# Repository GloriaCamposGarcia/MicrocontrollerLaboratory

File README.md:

# Microcontroller Laboratory :)

## Introduction

Microcontrollers are all around  he world. Each day, Microcontrollers, are more present in the many aspects of our lives: in our work, inside our houses, and in more. We can find them controlling small devices like cellphones, microwaves, washing machines, and televisions.

A microcontroller is one device or chip that is used to govern one or more processes. For example, the controller that regulates the room temperature of an air conditioner; it has a sensor that continuously measures the internal temperature and, when the preset limits are exceeded, it generates the necessary signals to adjust the temperature.

## State of the Art

### The practices and the PIC microcontroller

The main objective of this practices is to provide students the foundation to fully understand the operation of the PIC18F45K50 microcontroller. This will be achieved through 11 documents that will guide the reader to create their own electronic card or Printed Circuit Board (PCB) and to be able to program it; in order to, execute different functions.

The advantages of ta PIC microcontroller to others on the market, which is why it will be used throughout this manual, are as follows:

- Easy to operate.
- There is enough documentation to work with it and it’s easy to obtain it.
- The price is comparatively lower than its competitors.
- It has a high operating speed.
- Development tools are cheap and easy to use.
- There are a variety of hardware that can record, erase and check the behavior of PIC.
- Once you learn to handle a PIC, it will easier to handle any other models of microcontrollers.

### KiCad EDA Software

KiCad is an open source software suite for Electronic Design Automation (EDA). The programs handle Schematic Capture,
and PCB Layout with Gerber output. The suite runs on Windows, Linux and macOS and is licensed under GNU GPL v3. The
first release date was in 1992 by its original author, Jean-Pierre Charras, but is now currently under development by
the KiCad Developers Team.

## Evaluation

- Demonstation  ... 60%
- Report .......... 40%

## Submission

Every submission must be in your own github repository. If you which you could fork this as skeleton. All pull request
will be denied.

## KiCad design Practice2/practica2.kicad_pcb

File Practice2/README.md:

# Practice 2. Developiong the PCB (Layout)

## Objectives

Develop the connection diagrams (layout) from the schematic diagram.

## Introduction

Microcontrollers are all around  he world. Each day, Microcontrollers, are more present in the many aspects of our lives: in our work, inside our houses, and in more. We can find them controlling small devices like cellphones, microwaves, washing machines, and televisions.

A microcontroller is one device or chip that is used to govern one or more processes. For example, the controller that regulates the room temperature of an air conditioner; it has a sensor that continuously measures the internal temperature and, when the preset limits are exceeded, it generates the necessary signals to adjust the temperature.

## State of the Art

### The practices and the PIC microcontroller

The main objective of this practices is to provide students the foundation to fully understand the operation of the PIC18F45K50 microcontroller. This will be achieved through 11 documents that will guide the reader to create their own electronic card or Printed Circuit Board (PCB) and to be able to program it; in order to, execute different functions.

The advantages of ta PIC microcontroller to others on the market, which is why it will be used throughout this manual, are as follows:

- Easy to operate.
- There is enough documentation to work with it and it’s easy to obtain it.
- The price is comparatively lower than its competitors.
- It has a high operating speed.
- Development tools are cheap and easy to use.
- There are a variety of hardware that can record, erase and check the behavior of PIC.
- Once you learn to handle a PIC, it will easier to handle any other models of microcontrollers.

### KiCad EDA Software

KiCad is an open source software suite for Electronic Design Automation (EDA). The programs handle Schematic Capture,
and PCB Layout with Gerber output. The suite runs on Windows, Linux and macOS and is licensed under GNU GPL v3. The
first release date was in 1992 by its original author, Jean-Pierre Charras, but is now currently under development by
the KiCad Developers Team. 

## Results

In this section, you must report the outcomes of the laboratory activities.

### Follow the next 'Project Configuration' Steps

1. In  the  same  project  from  practice  1,  click  on  the  icon ‘Assign PCB footprints to schematic symbols’.  By  doing  so,  you  will  be  able  to  watch  the  footprints associations in a list format. ***NOTE:*** *If a ***‘Confirmation’*** window pops to reassign all the components to a new library format, click ‘No.’*

2. Now it is time to add the corresponding libraries to the Cvpcbprogram.   Download from [here](./modules)  the modules   needed   for   the   project.   Click   on Preferences→Manage Footprint Libraries...and  in this  way  you  will  be  able  to  add  the  modules  from the folder  named  ‘modules.’  Click  on  ‘Project  Specific Libraries...’  tab,  then  click  on  the  button  ‘Browse Libraries...’ and search for the folder  where  you  save the modules. Select all the files and click ‘OK.’Fig.  1 shows the result of the added modules. NOTE:Your KiCad EDA Software must be in english to add the modules.

3. Once  that  is  done,  you  must  associate  the  list  of components  with  its  respective  footprint using Table  I for  guidance.  Be  sure  to  activate  the  option  ‘Filter footprints  list  by  library’ from  the Cvpcbtoolbar. To associate  the  components  showed  in  the middle  column,  double  click  with  their  corresponding footprint from the right column. ***NOTE:*** *Search  all  the  footprints  in  the*  ***‘user’*** *and * 
***‘discrete’*** * added libraries that should be found at the end of the list.*

4. Save   your modifications  by  clicking  **‘Apply,  Save Schematic & Continue,’ and then click ‘OK.’**
5. After that, you may close the Cvpcband go back to the EESchema (Schematic  Editor.)  Save  your  project  by clicking   on File→Save.   Close   the   editor   of   the Schematic and switch back to the **‘Project Manager.’**

6. Once you have the design of the circuit on the schematic, it is time to generate the **‘layout’** of our PCB  using the Netlist  file. On  the Project  Manager program  from KiCad, click on the icon **‘PCB layout editor’** . A new window will appear from the PCBNew. Click **‘Yes’** in the confirmation window.
7. On  the  toolbar  menu  from  the PCBNew click  on  the **‘Page  Settings  for  paper  size  and  texts’**
and modify the size settings to **‘USLetter 8.5x11in.’**

8. After  that,  it  will be  time  to  focus  more  on  design concepts.  You  may  do  so  by  opening  the
menu  of **‘Setup→Design Rules...’**. On   it,   some   final   design characteristics will appear with many millimeter values. Between   them,   you   should   find  the  **‘Clearance’** specification  which  is  the  smallest  spaces  that  it  must exist  between  the tracks  on the  PCB.  You  shall  set the value of this cell to 0.508 mm (0.020 inches.) Next, we set  a  value  of 1.200  mm  (0.047244 inches)on the  cell of **‘Track Width.’** 

9. Switch now to the ‘Global Design Rules’ tab and write, if needed, the minimum values for each an every one of the parameters on the ‘Minimum Allowed Values’ box. Click ‘OK.’

10. Time  to  import  the  Netlist  file.  Go  to  the  toolbar ‘Tools→Update  PCB  from  Schematic...’  and  then click on ‘Update  PCB.’ When  you  close  the  window all the components will appear on the screen.

11.Check in the ‘Layers Manager’ window (located at the right  part  of  your  screen) that all  the needed  boxes  are
checked, as shown:

11.Check in the ‘Layers Manager’ window (located at the right  part  of  your  screen) that all  the needed  boxes  are checke

12. Now you  have  to  define  the  limits  of  the  PCB.  First, highlight  the  ‘Edge.Cuts’  layer.  Then,  select  the  ‘Add  graphic lines’ tool and began to trace the original measures of your copper board (15x20 cm.) You must also define the  cutting  area;  do  not  forget  to  add  a  2.5  cm  margin around the board. To measure the lines, you can use the ‘Add dimension’ tool located on the right.

13. It is your turn to move all the components in the circuit in  order  to  avoid  any  track  intersection  inside  the working   area.   You   can   move   the   components   by positioning your mouse pointer above it and pressing the key [G]. All the components are connected to each other by a group of wires called ratsnest. Make sure that the icon  of  **‘Hide  board  ratsnest’** located  in  the toolbar of the left is highlighted.

14. Now you must link all the connections of you PCB. But before  that,  you  must  change  the  drawing  option  from the right toolbar from ‘Edge.Cuts’ to ‘B.Cu (PgDn)’ (B->Bottom, Cu->Copper.).

15. Start to connect your tracks to each and every one pin on the schematic by using the icon ‘Route Tracks’. Trace  all  the  routes  for  each  net  or  connection  in  your PCB design.

16. Once  your  are  done,  save  your  layout  File->Save  or using the command [Ctrl + S].

17. Your board must look like:

### Report
For this practice, modify only the Conclusion section. Commit an push the changes on the fork of this repository and add
upload the link on Canvas.

### File uploads
Commit and push the files with extensions .pro and .kicad_pcb created once you completed all the steps of the document in the repository.

### Demonstration
Screenshot the image of the complete schematic and upload it at the repository.

## Conclusion

La parte de los footprimts fue la parte mas complicada debido a que no me identificaba las librerias y la parte de las capas al momento de hacer la conexion se pudo ver la importancia al final al ver el esquematico completo, creo que hace falta alguna herrameinta para hacer el margen y no solo poder poner dimensiones ya que lo hace mas impreciso y tedioso, fuera de eso las conexciones estan muy bien identificada para hacer la union entrre todos los componentes. Sin embargo una modificacion extra que tuve que realizar fue la modificacion del tamaño de la hoja ya que me quedaban los tamaños y elementos muy justos pra la realizacion del margen con el tamaño de hoja anterior o se sobreponian ciertos elementos haciendo la colocacion mas complicada.

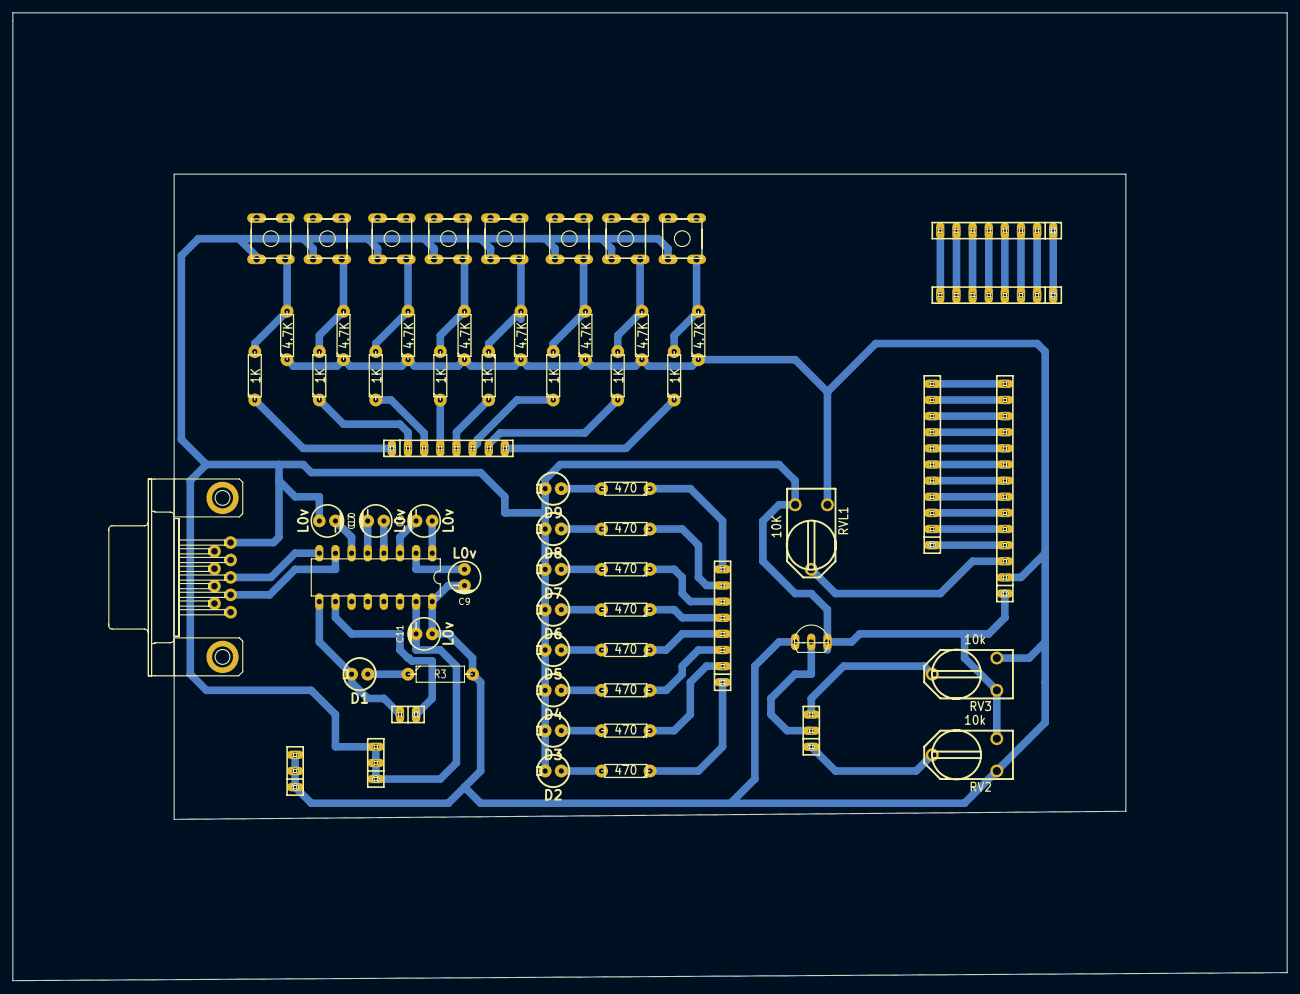
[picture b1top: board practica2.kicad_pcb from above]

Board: 2 copper layers, 200.7 x 152.4 mm, 63 parts (0 on the bottom side), 68 nets.

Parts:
C6, C7, C9, C11: L0v; Capacitor_elect
CL0: L0v; Capacitor_elect
D1, D2, D3, D4, D5, D6, D7, D8, D9: LED; Led
JP2, JP3, JP11, JP14: PINHD-1X8; pinhead-1X08
JP5: PINHD-1X2; pinhead-1X02
JP9, JP10, JP15: PINHD-1X3; pinhead-1X03
JP12: PINHD-1X14; pinhead-1X14
JP13: PINHD-1X11; pinhead-1X11
R3: 470; Resistor_large
R4, R5, R6, R7, R8, R9, R10, R11: 470; Resistor
R20, R21, R22, R23, R24, R25, R26, R27: 4.7K; Resistor
RL2, RL3, RL4, RL5, RL6, RL7, RL8, RL9: 1K; Resistor
RV2, RV3: 10k; RV2X4
RVL1: 10K; RV2X4
S2, S3, S4, S5, S6, S7, S8, S9: DTS-6
U3: MCP9700A
U4: MAX232; Maxim232
X2: F09HP; Conector_F09HP

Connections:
+5VA: C9.2, C11.1, JP9.1, JP9.2, JP9.3, JP12.2, R3.2, R20.1, R21.1, R22.1, R23.1, R24.1, R25.1, R26.1, R27.1, RV2.1, RV3.3, RVL1.1, U3.1, U4.16
GNDA: C11.2, CL0.1, D2.2, D3.2, D4.2, D5.2, D6.2, D7.2, D8.2, D9.2, JP10.1, JP10.2, JP10.3, JP12.1, RV2.3, RV3.1, RVL1.3, S2.1, S3.1, S4.1, S5.1, S6.1, S7.1, S8.1, S9.1, U3.3, U4.15, X2.5
unnamed: C6.1, U4.1
unnamed: C6.2, U4.3
unnamed: C7.1, U4.4
unnamed: C7.2, U4.5
unnamed: C9.1, U4.2
unnamed: CL0.2, U4.6
unnamed: D1.1, R3.1
unnamed: D1.2, JP5.2, U4.9
unnamed: D2.1, R11.2
unnamed: D3.1, R10.2
unnamed: D4.1, R9.2
unnamed: D5.1, R8.2
unnamed: D6.1, R7.2
unnamed: D7.1, R6.2
unnamed: D8.1, R5.2
unnamed: D9.1, R4.2
unnamed: JP2.1, JP3.1
unnamed: JP2.2, JP3.2
unnamed: JP2.3, JP3.3
unnamed: JP2.4, JP3.4
unnamed: JP2.5, JP3.5
unnamed: JP2.6, JP3.6
unnamed: JP2.7, JP3.7
unnamed: JP2.8, JP3.8
unnamed: JP5.1, U4.10
unnamed: JP11.1, R11.1
unnamed: JP11.2, R10.1
unnamed: JP11.3, R9.1
unnamed: JP11.4, R8.1
unnamed: JP11.5, R7.1
unnamed: JP11.6, R6.1
unnamed: JP11.7, R5.1
unnamed: JP11.8, R4.1
unnamed: JP12.3, RVL1.2
unnamed: JP12.4, JP13.1
unnamed: JP12.5, JP13.2
unnamed: JP12.6, JP13.3
unnamed: JP12.7, JP13.4
unnamed: JP12.8, JP13.5
unnamed: JP12.9, JP13.6
unnamed: JP12.10, JP13.7
unnamed: JP12.11, JP13.8
unnamed: JP12.12, JP13.9
unnamed: JP12.13, JP13.10
unnamed: JP12.14, JP13.11
unnamed: JP14.1, RL2.1
unnamed: JP14.2, RL3.1
unnamed: JP14.3, RL4.1
unnamed: JP14.4, RL5.1
unnamed: JP14.5, RL6.2
unnamed: JP14.6, RL7.1
unnamed: JP14.7, RL8.1
unnamed: JP14.8, RL9.1
unnamed: JP15.1, RV2.2
unnamed: JP15.2, U3.2
unnamed: JP15.3, RV3.2
unnamed: R20.2, RL2.2, S2.3
unnamed: R21.2, RL3.2, S3.3
unnamed: R22.2, RL4.2, S4.3
unnamed: R23.2, RL5.2, S5.3
unnamed: R24.2, RL6.1, S6.3
unnamed: R25.2, RL7.2, S7.3
unnamed: R26.2, RL8.2, S8.3
unnamed: R27.2, RL9.2, S9.3
unnamed: U4.7, X2.2
unnamed: U4.8, X2.3

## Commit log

2020-09-20 Create prueba
2020-09-20 Create prueba2
2020-09-20 Create prueba3
